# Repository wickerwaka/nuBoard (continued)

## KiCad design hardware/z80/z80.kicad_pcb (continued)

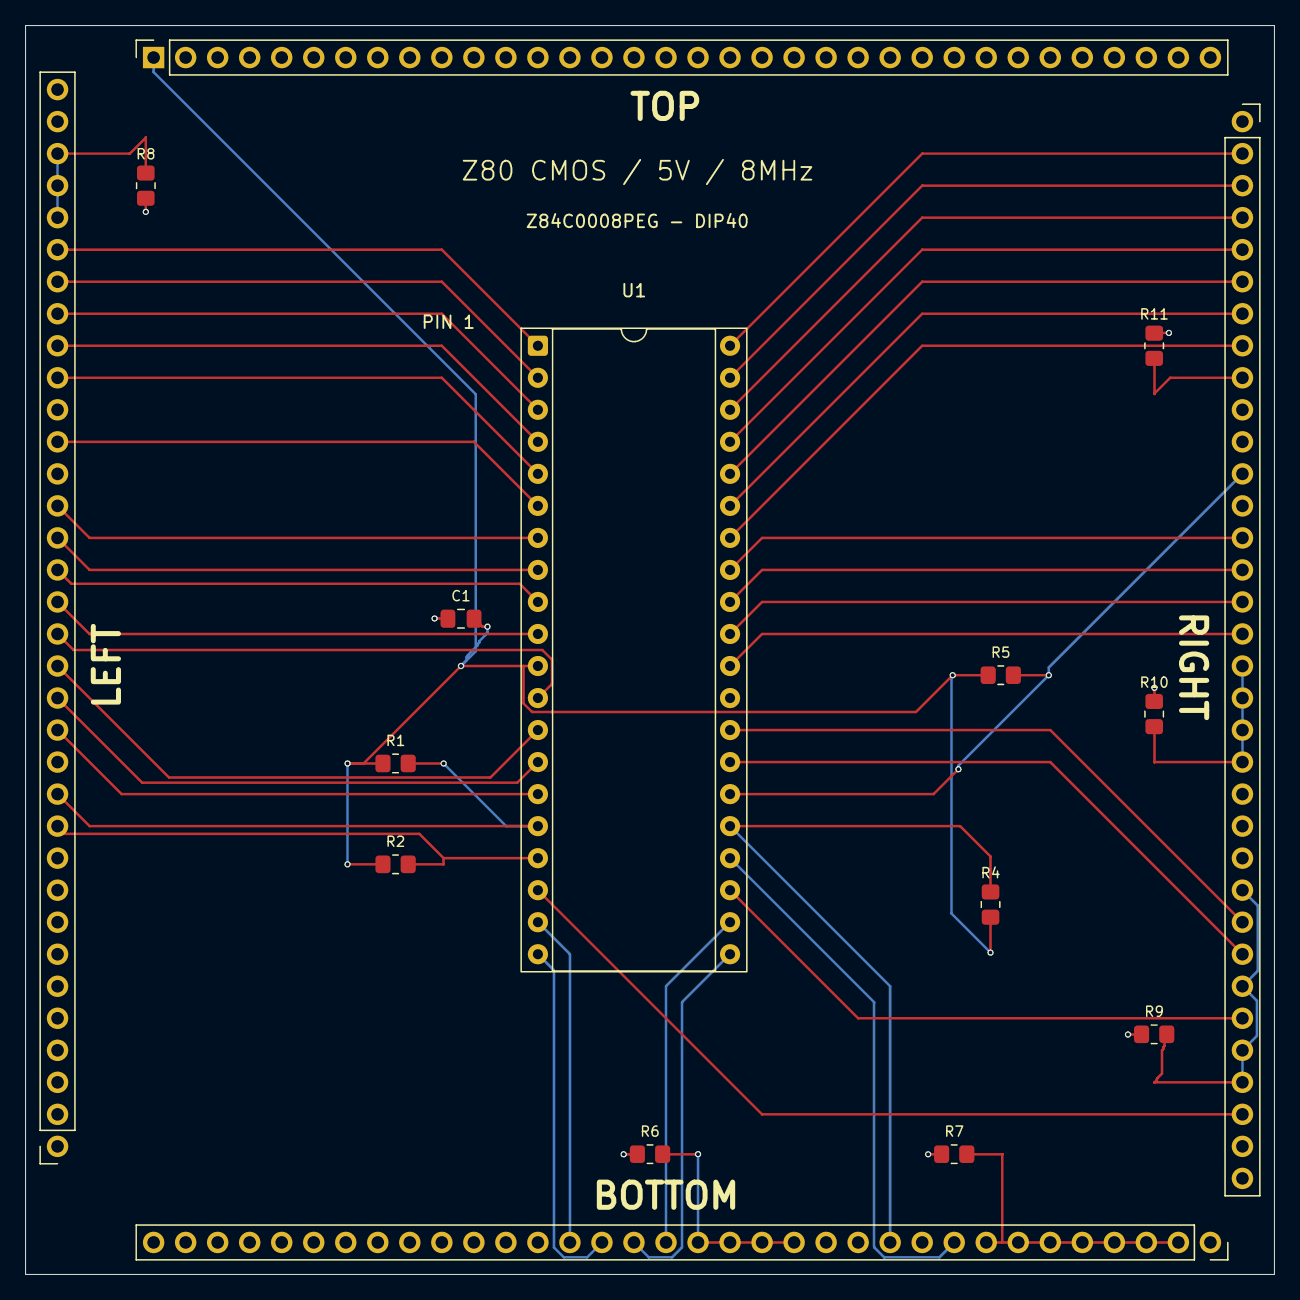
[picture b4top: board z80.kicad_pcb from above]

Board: 2 copper layers, 99.1 x 99.1 mm, 13 parts (0 on the bottom side), 46 nets.

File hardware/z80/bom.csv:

Reference,Quantity,Value/part,Package,Notes
U1,1,Z84C0008PEG,"DIP-40, 15.24mm rows",Use matching through-hole socket
C1,1,100nF ceramic 50V,0805 SMD HandSolder,Local supply bypass
R1 R2 R4 R5,4,10k >=0.25W,0805 SMD HandSolder,X0–X3 input pull-ups
J1,1,nuBoard mezzanine mating contact set,Four 34-position rows 2.54mm pitch,Match existing host
R6,1,47k 1% >=0.25W,0805 SMD HandSolder,B1 shared unused-bit pull-down to GND
R7,1,47k 1% >=0.25W,0805 SMD HandSolder,B2 shared unused-bit pull-down to GND
R8,1,47k 1% >=0.25W,0805 SMD HandSolder,L0 shared unused-bit pull-down to GND
R9,1,47k 1% >=0.25W,0805 SMD HandSolder,R0 shared unused-bit pull-down to GND
R10,1,47k 1% >=0.25W,0805 SMD HandSolder,R1 shared unused-bit pull-down to GND
R11,1,47k 1% >=0.25W,0805 SMD HandSolder,R2 shared unused-bit pull-down to GND

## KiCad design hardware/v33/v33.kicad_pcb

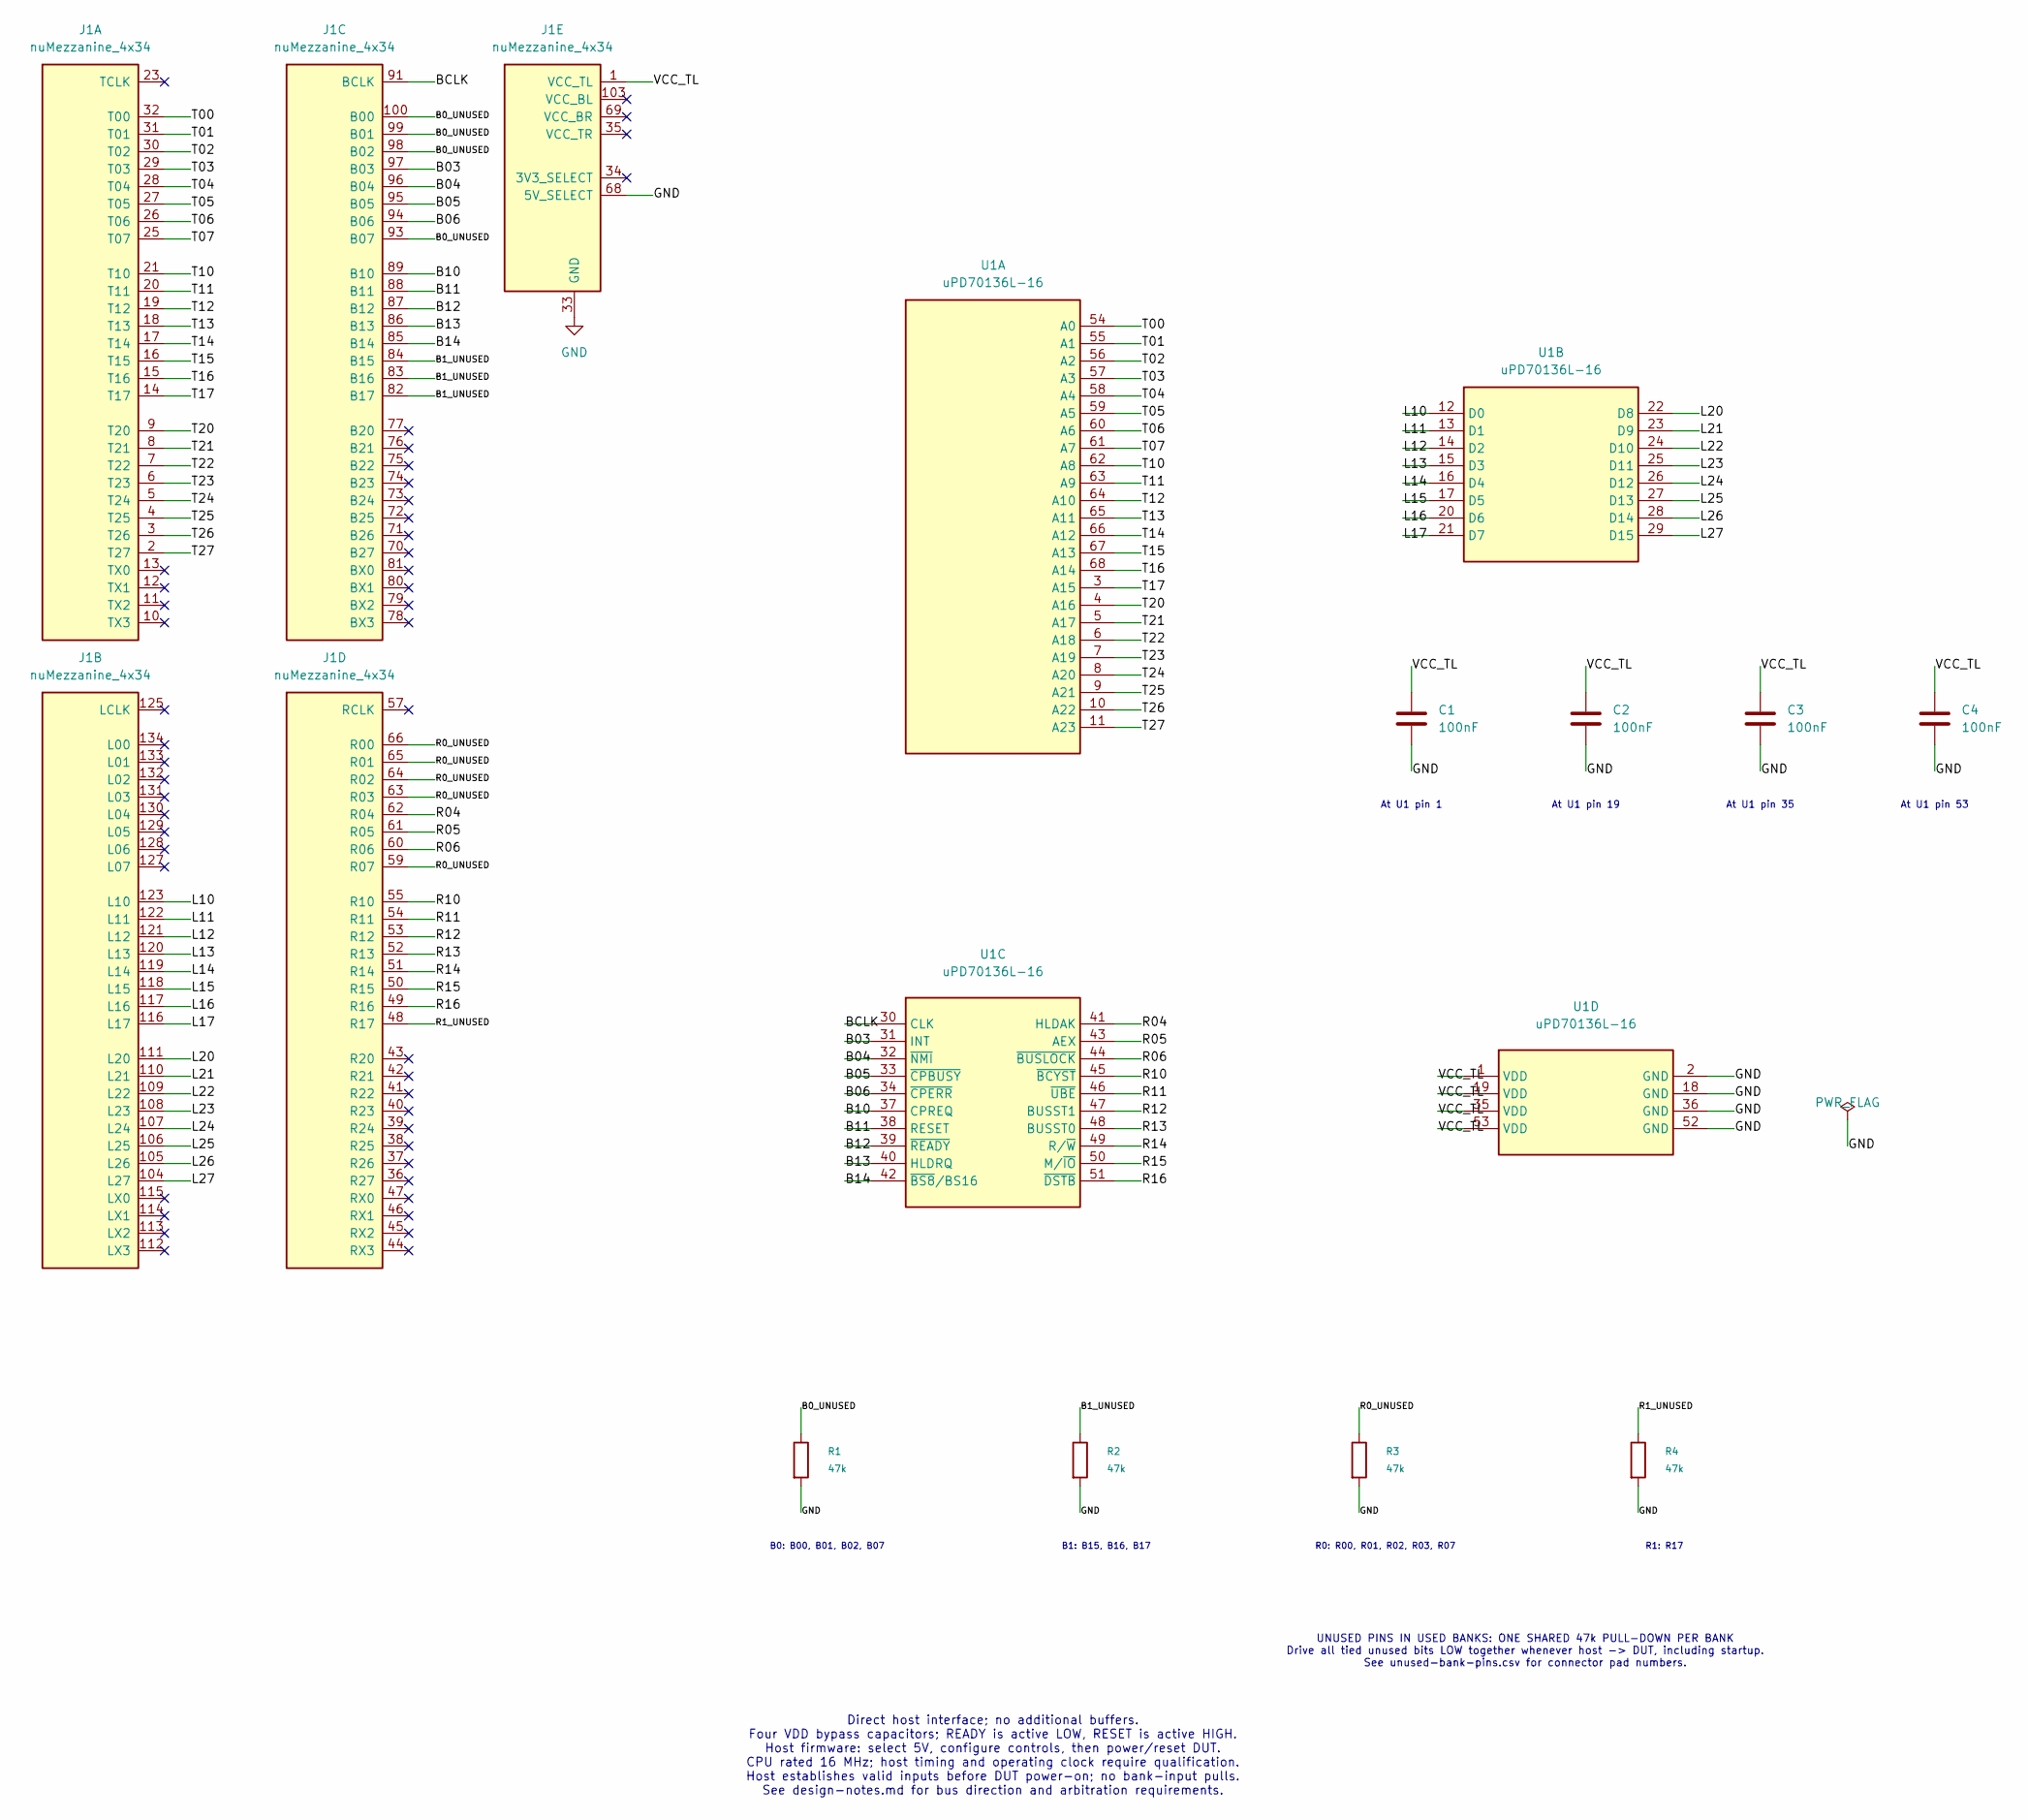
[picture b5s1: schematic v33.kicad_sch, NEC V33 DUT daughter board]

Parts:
C1, C2, C3, C4: 100nF; C_0805_2012Metric_Pad1.18x1.45mm_HandSolder; Voltage 50V
J1: nuMezzanine_4x34; nuMezzanine_4x34_P2.54mm
R1, R2, R3, R4: 47k; R_0805_2012Metric_Pad1.20x1.40mm_HandSolder
U1: uPD70136L-16; PLCC-68_THT-Socket

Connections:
/B0_UNUSED: J1.93 (B07_93), J1.98 (B02_98), J1.99 (B01_99), J1.100 (B00_100), R1.1
/B1_UNUSED: J1.82 (B17_82), J1.83 (B16_83), J1.84 (B15_84), R2.1
/B03: J1.97 (B03_97), U1.31 (INT)
/B04: J1.96 (B04_96), U1.32 (~NMI)
/B05: J1.95 (B05_95), U1.33 (~CPBUSY)
/B06: J1.94 (B06_94), U1.34 (~CPERR)
/B10: J1.89 (B10_89), U1.37 (CPREQ)
/B11: J1.88 (B11_88), U1.38 (RESET)
/B12: J1.87 (B12_87), U1.39 (~READY)
/B13: J1.86 (B13_86), U1.40 (HLDRQ)
/B14: J1.85 (B14_85), U1.42 (~BS8/BS16)
/BCLK: J1.91 (BCLK_91), U1.30 (CLK)
/L10: J1.123 (L10_123), U1.12 (D0)
/L11: J1.122 (L11_122), U1.13 (D1)
/L12: J1.121 (L12_121), U1.14 (D2)
/L13: J1.120 (L13_120), U1.15 (D3)
/L14: J1.119 (L14_119), U1.16 (D4)
/L15: J1.118 (L15_118), U1.17 (D5)
/L16: J1.117 (L16_117), U1.20 (D6)
/L17: J1.116 (L17_116), U1.21 (D7)
/L20: J1.111 (L20_111), U1.22 (D8)
/L21: J1.110 (L21_110), U1.23 (D9)
/L22: J1.109 (L22_109), U1.24 (D10)
/L23: J1.108 (L23_108), U1.25 (D11)
/L24: J1.107 (L24_107), U1.26 (D12)
/L25: J1.106 (L25_106), U1.27 (D13)
/L26: J1.105 (L26_105), U1.28 (D14)
/L27: J1.104 (L27_104), U1.29 (D15)
/R0_UNUSED: J1.59 (R07_59), J1.63 (R03_63), J1.64 (R02_64), J1.65 (R01_65), J1.66 (R00_66), R3.1
/R1_UNUSED: J1.48 (R17_48), R4.1
/R04: J1.62 (R04_62), U1.41 (HLDAK)
/R05: J1.61 (R05_61), U1.43 (AEX)
/R06: J1.60 (R06_60), U1.44 (~BUSLOCK)
/R10: J1.55 (R10_55), U1.45 (~BCYST)
/R11: J1.54 (R11_54), U1.46 (~UBE)
/R12: J1.53 (R12_53), U1.47 (BUSST1)
/R13: J1.52 (R13_52), U1.48 (BUSST0)
/R14: J1.51 (R14_51), U1.49 (R/~W)
/R15: J1.50 (R15_50), U1.50 (M/~IO)
/R16: J1.49 (R16_49), U1.51 (~DSTB)
/T00: J1.32 (T00_32), U1.54 (A0)
/T01: J1.31 (T01_31), U1.55 (A1)
/T02: J1.30 (T02_30), U1.56 (A2)
/T03: J1.29 (T03_29), U1.57 (A3)
/T04: J1.28 (T04_28), U1.58 (A4)
/T05: J1.27 (T05_27), U1.59 (A5)
/T06: J1.26 (T06_26), U1.60 (A6)
/T07: J1.25 (T07_25), U1.61 (A7)
/T10: J1.21 (T10_21), U1.62 (A8)
/T11: J1.20 (T11_20), U1.63 (A9)
/T12: J1.19 (T12_19), U1.64 (A10)
/T13: J1.18 (T13_18), U1.65 (A11)
/T14: J1.17 (T14_17), U1.66 (A12)
/T15: J1.16 (T15_16), U1.67 (A13)
/T16: J1.15 (T16_15), U1.68 (A14)
/T17: J1.14 (T17_14), U1.3 (A15)
/T20: J1.9 (T20_9), U1.4 (A16)
/T21: J1.8 (T21_8), U1.5 (A17)
/T22: J1.7 (T22_7), U1.6 (A18)
/T23: J1.6 (T23_6), U1.7 (A19)
/T24: J1.5 (T24_5), U1.8 (A20)
/T25: J1.4 (T25_4), U1.9 (A21)
/T26: J1.3 (T26_3), U1.10 (A22)
/T27: J1.2 (T27_2), U1.11 (A23)
/VCC_TL: C1.1, C2.1, C3.1, C4.1, J1.1 (VCC_TL_1), U1.1 (VDD), U1.19 (VDD), U1.35 (VDD), U1.53 (VDD)
GND: C1.2, C2.2, C3.2, C4.2, J1.22 (GND_22), J1.24 (GND_24), J1.33 (GND_33), J1.56 (GND_56), J1.58 (GND_58), J1.67 (GND_67), J1.68 (5V_SELECT_68), J1.90 (GND_90), J1.92 (GND_92), J1.101 (GND_101), J1.102 (GND), J1.124 (GND_124), J1.126 (GND_126), J1.135 (GND_135), J1.136 (GND), R1.2, R2.2, R3.2, R4.2, U1.2 (GND), U1.18 (GND), U1.36 (GND), U1.52 (GND)

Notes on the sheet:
At U1 pin 1
At U1 pin 19
At U1 pin 35
At U1 pin 53
Direct host interface; no additional buffers. Four VDD bypass capacitors; READY is active LOW, RESET is active HIGH. Host firmware: select 5V, configure controls, then power/reset DUT. CPU rated 16 MHz; host timing and operating clock require qualification. Host establishes valid inputs before DUT 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
B0: B00, B01, B02, B07
B1: B15, B16, B17
R0: R00, R01, R02, R03, R07
R1: R17
UNUSED PINS IN USED BANKS: ONE SHARED 47k PULL-DOWN PER BANK Drive all tied unused bits LOW together whenever host -> DUT, including startup. See unused-bank-pins.csv for connector pad numbers.

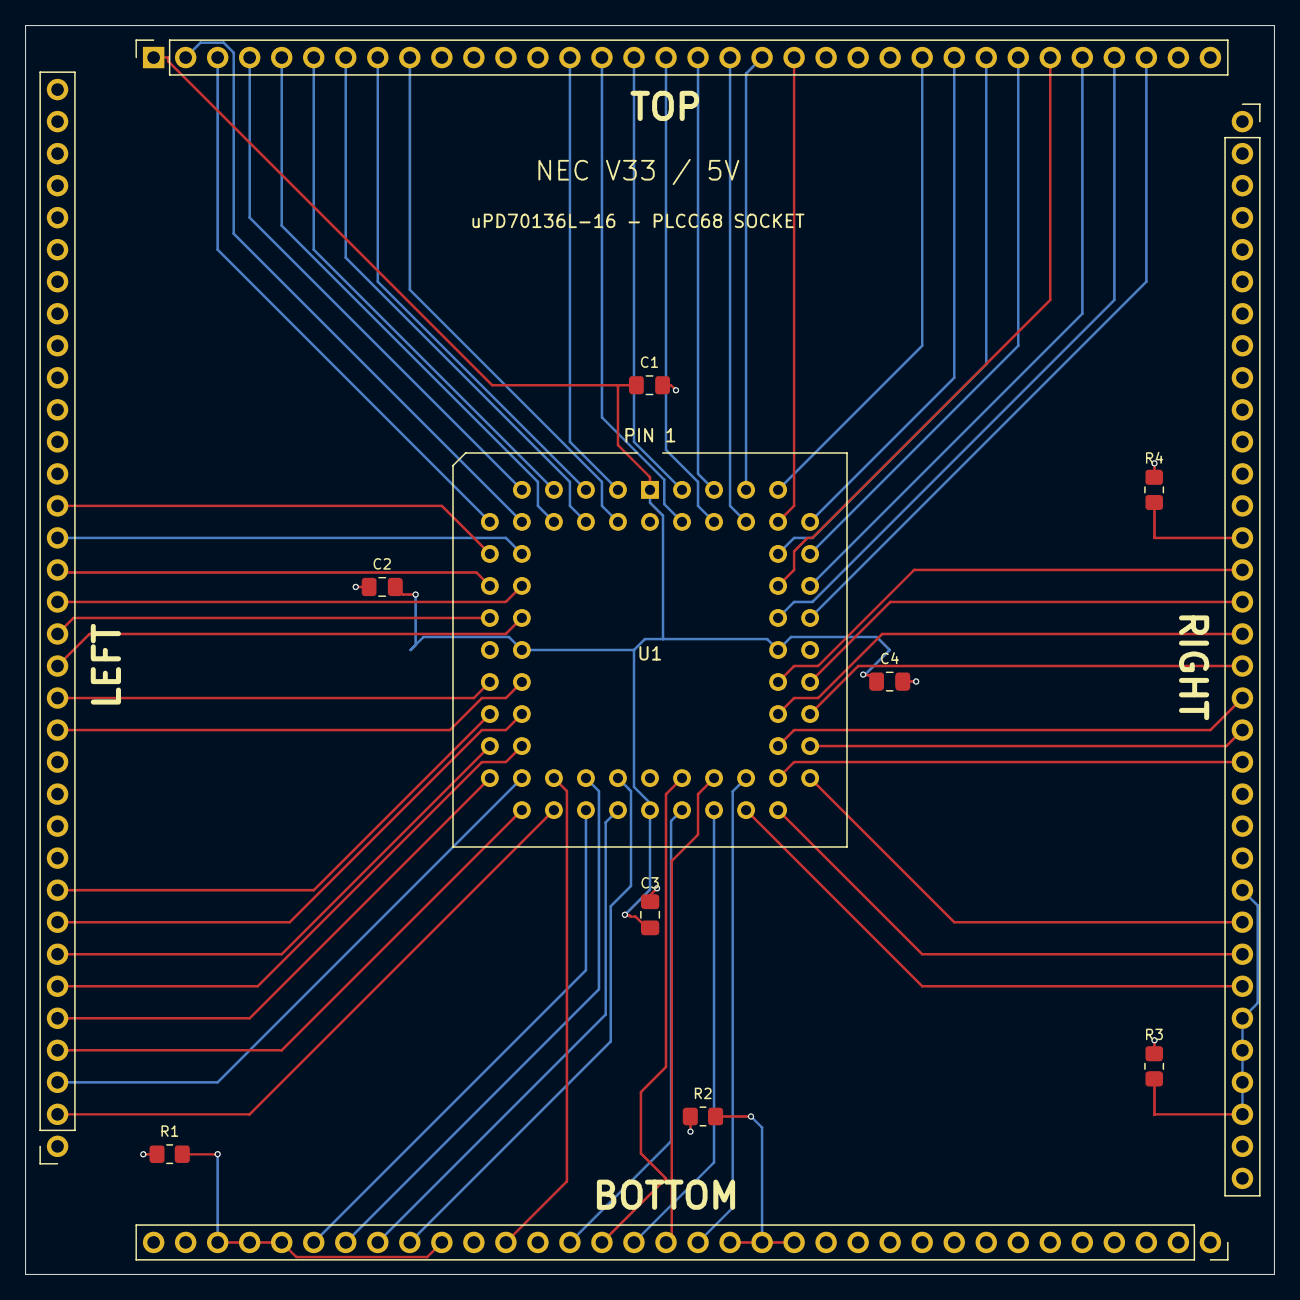
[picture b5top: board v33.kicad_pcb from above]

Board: 2 copper layers, 99.1 x 99.1 mm, 10 parts (0 on the bottom side), 66 nets.

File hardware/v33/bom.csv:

References,Quantity,Part / specification,Assembly note
U1,1,NEC uPD70136L-16,68-pin PLCC; user-supplied DUT
U1 socket,1,Assmann A-CCS 068-Z-T,Through-hole PLCC-68 socket; pin 1 toward TOP
C1 C2 C3 C4,4,"100 nF ceramic 50 V, 0805 SMD HandSolder",Enlarged hand-solder pads; top-side placement
J1,1,Template nuMezzanine_4x34 edge interface,Populate mating hardware to match existing host/template
R1,1,"47k 1% >=0.25W, 0805 SMD HandSolder",B0 shared unused-bit pull-down to GND
R2,1,"47k 1% >=0.25W, 0805 SMD HandSolder",B1 shared unused-bit pull-down to GND
R3,1,"47k 1% >=0.25W, 0805 SMD HandSolder",R0 shared unused-bit pull-down to GND
R4,1,"47k 1% >=0.25W, 0805 SMD HandSolder",R1 shared unused-bit pull-down to GND

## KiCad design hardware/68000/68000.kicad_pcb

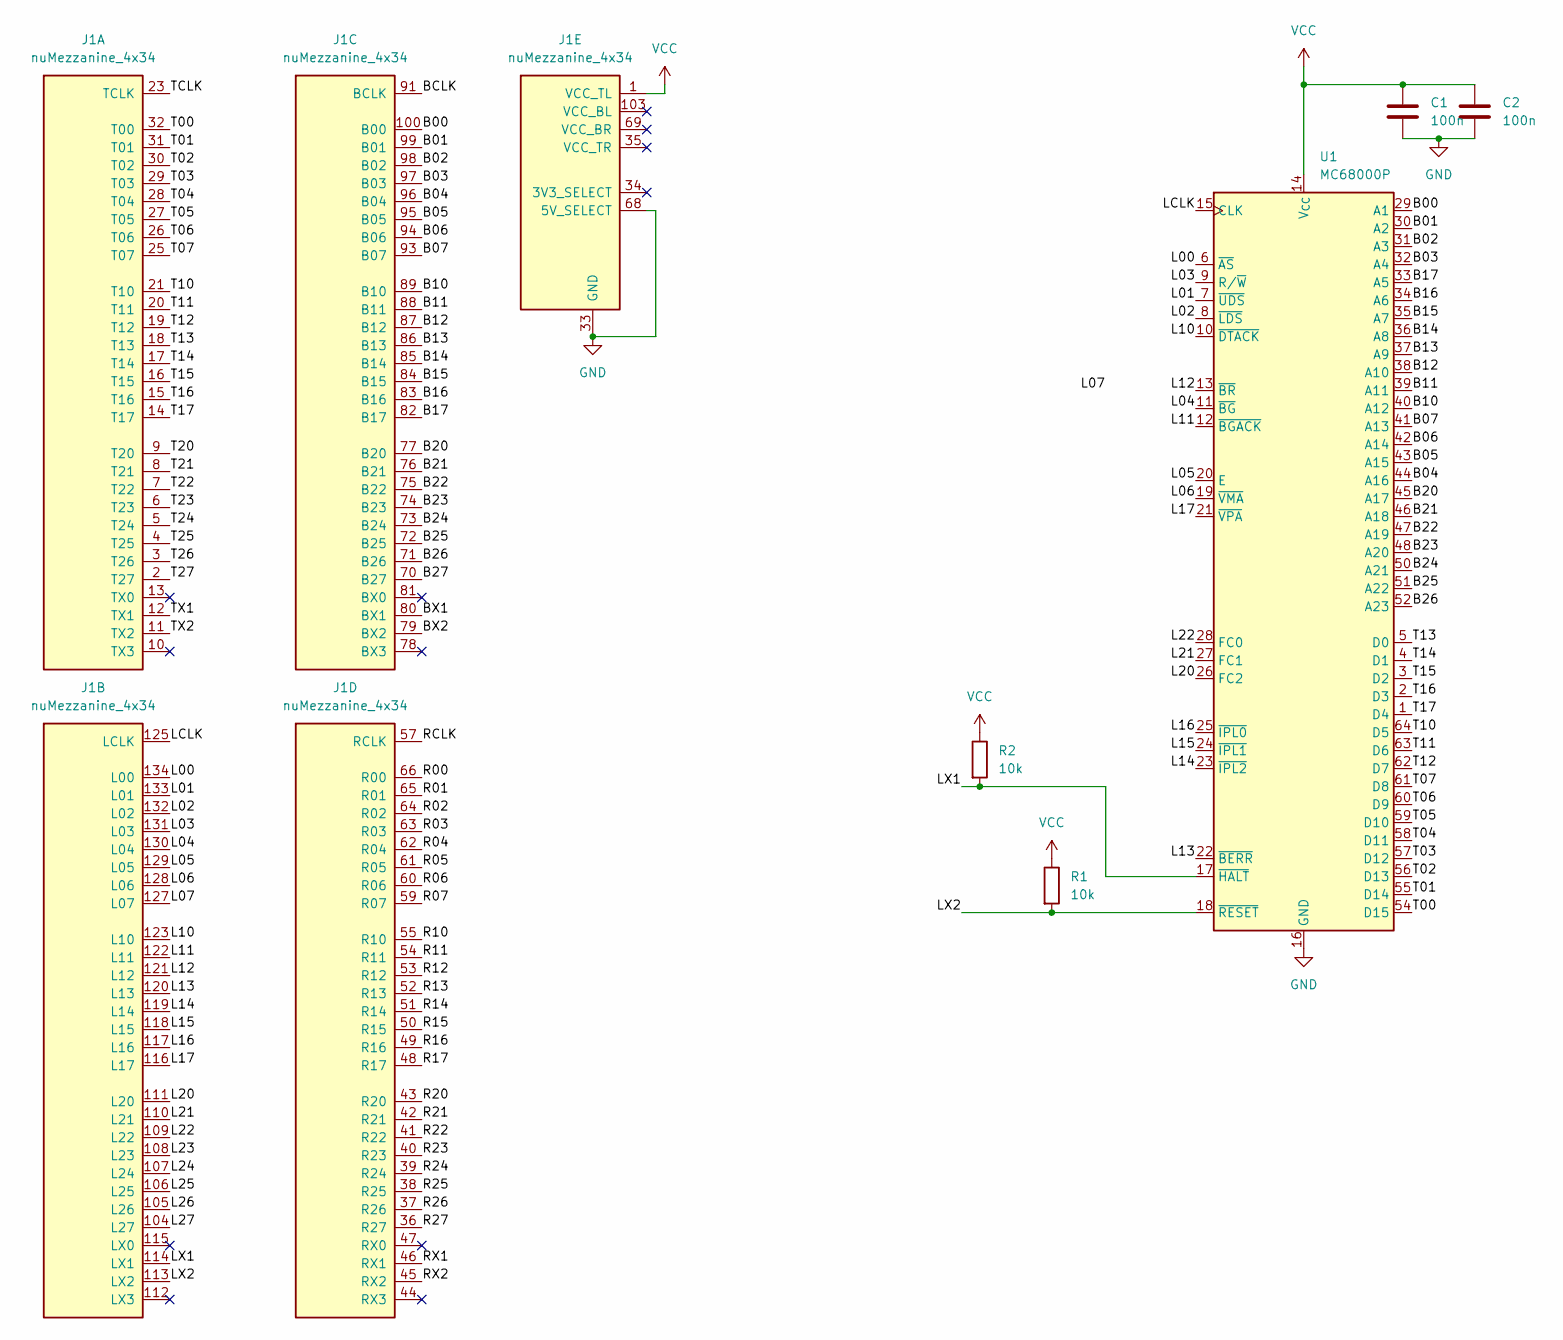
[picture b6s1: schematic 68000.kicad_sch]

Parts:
C1, C2: 100n; C_0805_2012Metric_Pad1.18x1.45mm_HandSolder
J1: nuMezzanine_4x34; nuMezzanine_4x34_P2.54mm
R1, R2: 10k; R_0805_2012Metric_Pad1.20x1.40mm_HandSolder
U1: MC68000P; DIP-64_W22.86mm

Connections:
/B00: J1.100 (B00_100), U1.29 (A1)
/B01: J1.99 (B01_99), U1.30 (A2)
/B02: J1.98 (B02_98), U1.31 (A3)
/B03: J1.97 (B03_97), U1.32 (A4)
/B04: J1.96 (B04_96), U1.44 (A16)
/B05: J1.95 (B05_95), U1.43 (A15)
/B06: J1.94 (B06_94), U1.42 (A14)
/B07: J1.93 (B07_93), U1.41 (A13)
/B10: J1.89 (B10_89), U1.40 (A12)
/B11: J1.88 (B11_88), U1.39 (A11)
/B12: J1.87 (B12_87), U1.38 (A10)
/B13: J1.86 (B13_86), U1.37 (A9)
/B14: J1.85 (B14_85), U1.36 (A8)
/B15: J1.84 (B15_84), U1.35 (A7)
/B16: J1.83 (B16_83), U1.34 (A6)
/B17: J1.82 (B17_82), U1.33 (A5)
/B20: J1.77 (B20_77), U1.45 (A17)
/B21: J1.76 (B21_76), U1.46 (A18)
/B22: J1.75 (B22_75), U1.47 (A19)
/B23: J1.74 (B23_74), U1.48 (A20)
/B24: J1.73 (B24_73), U1.50 (A21)
/B25: J1.72 (B25_72), U1.51 (A22)
/B26: J1.71 (B26_71), U1.52 (A23)
/B27: J1.70 (B27_70)
/BCLK: J1.91 (BCLK_91)
/BX1: J1.80 (BX1_80)
/BX2: J1.79 (BX2_79)
/L00: J1.134 (L00_134), U1.6 (~AS)
/L01: J1.133 (L01_133), U1.7 (~UDS)
/L02: J1.132 (L02_132), U1.8 (~LDS)
/L03: J1.131 (L03_131), U1.9 (R/~W)
/L04: J1.130 (L04_130), U1.11 (~BG)
/L05: J1.129 (L05_129), U1.20 (E)
/L06: J1.128 (L06_128), U1.19 (~VMA)
/L07: J1.127 (L07_127)
/L10: J1.123 (L10_123), U1.10 (~DTACK)
/L11: J1.122 (L11_122), U1.12 (~BGACK)
/L12: J1.121 (L12_121), U1.13 (~BR)
/L13: J1.120 (L13_120), U1.22 (~BERR)
/L14: J1.119 (L14_119), U1.23 (~IPL2)
/L15: J1.118 (L15_118), U1.24 (~IPL1)
/L16: J1.117 (L16_117), U1.25 (~IPL0)
/L17: J1.116 (L17_116), U1.21 (~VPA)
/L20: J1.111 (L20_111), U1.26 (FC2)
/L21: J1.110 (L21_110), U1.27 (FC1)
/L22: J1.109 (L22_109), U1.28 (FC0)
/L23: J1.108 (L23_108)
/L24: J1.107 (L24_107)
/L25: J1.106 (L25_106)
/L26: J1.105 (L26_105)
/L27: J1.104 (L27_104)
/LCLK: J1.125 (LCLK_125), U1.15 (CLK)
/LX1: J1.114 (LX1_114), R2.2, U1.17 (~HALT)
/LX2: J1.113 (LX2_113), R1.2, U1.18 (~RESET)
/R00: J1.66 (R00_66)
/R01: J1.65 (R01_65)
/R02: J1.64 (R02_64)
/R03: J1.63 (R03_63)
/R04: J1.62 (R04_62)
/R05: J1.61 (R05_61)
/R06: J1.60 (R06_60)
/R07: J1.59 (R07_59)
/R10: J1.55 (R10_55)
/R11: J1.54 (R11_54)
/R12: J1.53 (R12_53)
/R13: J1.52 (R13_52)
/R14: J1.51 (R14_51)
/R15: J1.50 (R15_50)
/R16: J1.49 (R16_49)
/R17: J1.48 (R17_48)
/R20: J1.43 (R20_43)
/R21: J1.42 (R21_42)
/R22: J1.41 (R22_41)
/R23: J1.40 (R23_40)
/R24: J1.39 (R24_39)
/R25: J1.38 (R25_38)
/R26: J1.37 (R26_37)
/R27: J1.36 (R27_36)
/RCLK: J1.57 (RCLK_57)
/RX1: J1.46 (RX1_46)
/RX2: J1.45 (RX2_45)
/T00: J1.32 (T00_32), U1.54 (D15)
/T01: J1.31 (T01_31), U1.55 (D14)
/T02: J1.30 (T02_30), U1.56 (D13)
/T03: J1.29 (T03_29), U1.57 (D12)
/T04: J1.28 (T04_28), U1.58 (D11)
/T05: J1.27 (T05_27), U1.59 (D10)
/T06: J1.26 (T06_26), U1.60 (D9)
/T07: J1.25 (T07_25), U1.61 (D8)
/T10: J1.21 (T10_21), U1.64 (D5)
/T11: J1.20 (T11_20), U1.63 (D6)
/T12: J1.19 (T12_19), U1.62 (D7)
/T13: J1.18 (T13_18), U1.5 (D0)
/T14: J1.17 (T14_17), U1.4 (D1)
/T15: J1.16 (T15_16), U1.3 (D2)
/T16: J1.15 (T16_15), U1.2 (D3)
/T17: J1.14 (T17_14), U1.1 (D4)
/T20: J1.9 (T20_9)
/T21: J1.8 (T21_8)
/T22: J1.7 (T22_7)
/T23: J1.6 (T23_6)
/T24: J1.5 (T24_5)
/T25: J1.4 (T25_4)
/T26: J1.3 (T26_3)
/T27: J1.2 (T27_2)
/TCLK: J1.23 (TCLK_23)
/TX1: J1.12 (TX1_12)
/TX2: J1.11 (TX2_11)
GND: C1.2, C2.2, J1.22 (GND_22), J1.24 (GND_24), J1.33 (GND_33), J1.56 (GND_56), J1.58 (GND_58), J1.67 (GND_67), J1.68 (5V_SELECT_68), J1.90 (GND_90), J1.92 (GND_92), J1.101 (GND_101), J1.102 (GND), J1.124 (GND_124), J1.126 (GND_126), J1.135 (GND_135), J1.136 (GND), U1.16 (GND), U1.53 (GND)
VCC: C1.1, C2.1, J1.1 (VCC_TL_1), R1.1, R2.1, U1.14 (V_{CC}), U1.49 (V_{CC})

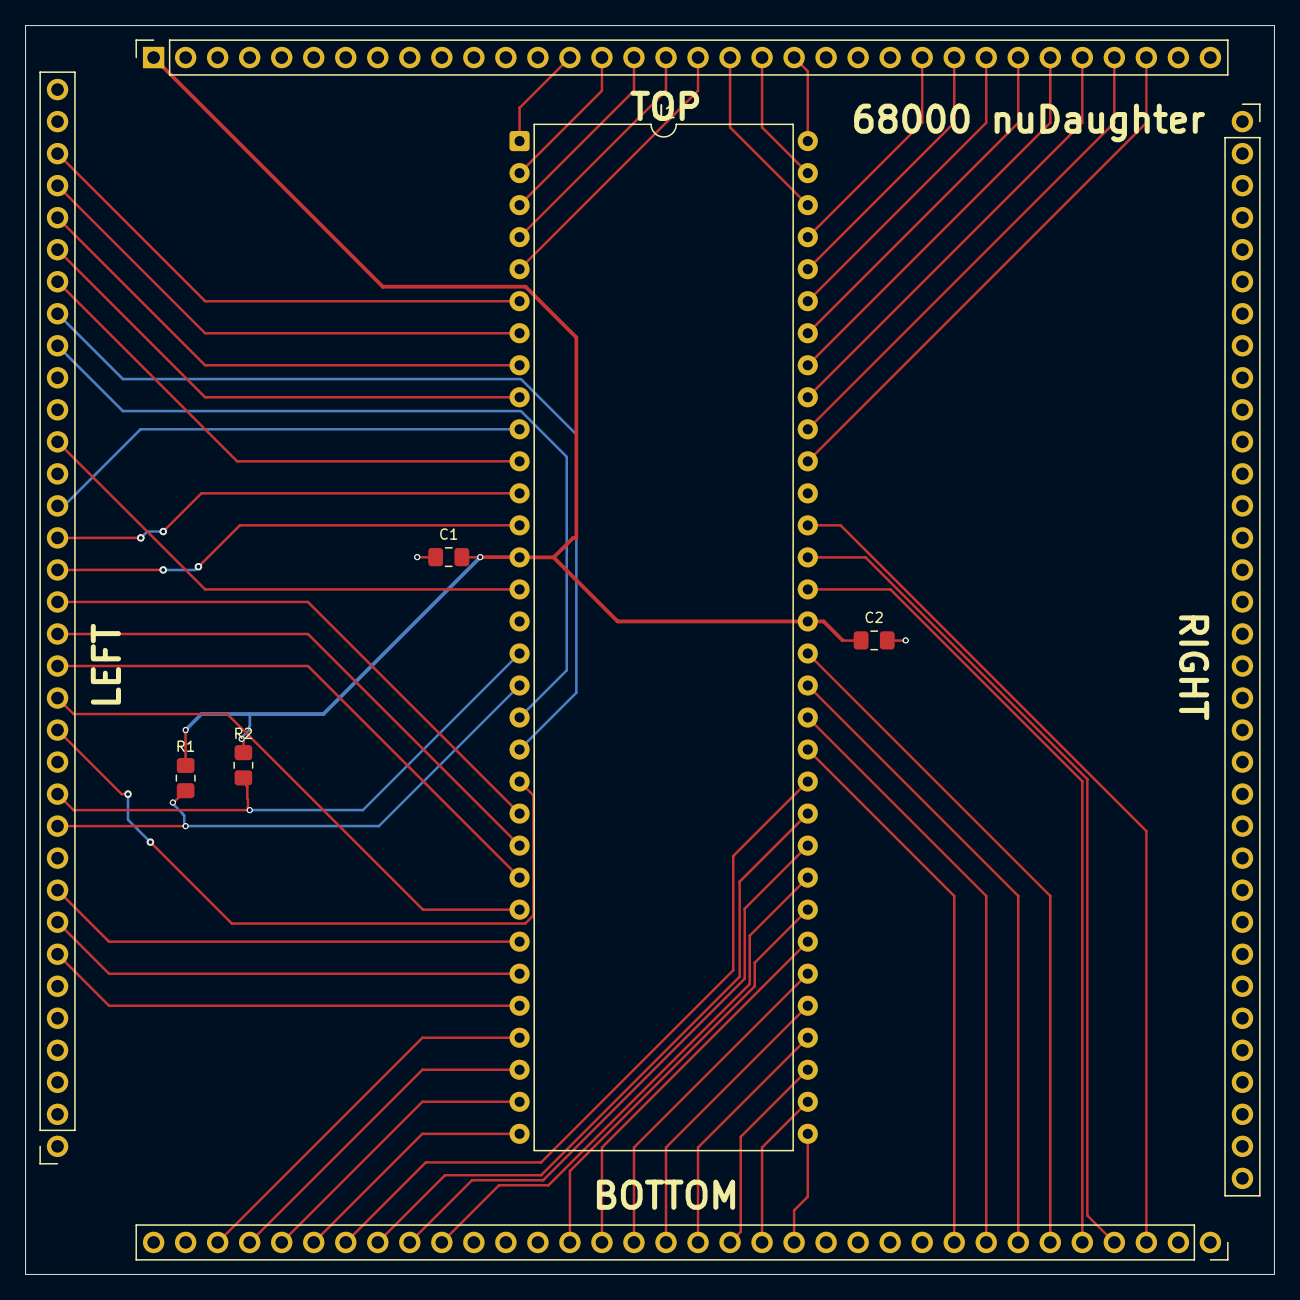
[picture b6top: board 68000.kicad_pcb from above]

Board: 2 copper layers, 99.1 x 99.1 mm, 6 parts (0 on the bottom side), 62 nets.

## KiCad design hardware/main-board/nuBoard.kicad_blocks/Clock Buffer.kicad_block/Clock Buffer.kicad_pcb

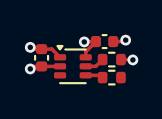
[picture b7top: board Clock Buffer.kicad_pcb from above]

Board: 6 copper layers, 5 parts (0 on the bottom side), 5 nets.

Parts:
C211, C212: 0.1u; C_0402_1005Metric
R57: 10K; R_0402_1005Metric
R58: 22; R_0402_1005Metric
U20: SN74LVC1T45DRL; SOT-563

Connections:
+3.3V: C211.1, U20.1 (VCCA)
/F_TCLK_EN: R57.1, U20.5 (DIR)
GND: C211.2, C212.2, R57.2, U20.2 (GND)
unnamed: R58.1, U20.4 (B)
VCCB: C212.1, U20.6 (VCCB)

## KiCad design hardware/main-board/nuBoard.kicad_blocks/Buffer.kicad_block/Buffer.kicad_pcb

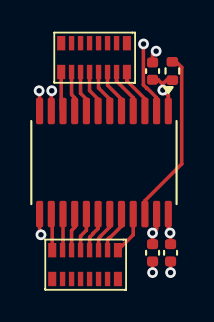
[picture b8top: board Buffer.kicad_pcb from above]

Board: 8 copper layers, 7 parts (0 on the bottom side), 20 nets.

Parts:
C68, C69, C70: 0.1u; C_0402_1005Metric
R35: 10K; R_0402_1005Metric
RN23, RN24: 22R; YC248-JR-0722RL
U24: SN74LVCH8T245PWR; TSSOP-24_4.4x7.8mm_P0.65mm

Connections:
+3.3V: C68.1, R35.1, U24.1 (VCCA)
/~F_B0_OE: R35.2, U24.22 (~OE)
GND: C68.2, C69.2, C70.2, U24.11 (GND), U24.12 (GND), U24.13 (GND)
unnamed: RN23.16, U24.3 (A1)
unnamed: RN23.15, U24.4 (A2)
unnamed: RN23.14, U24.5 (A3)
unnamed: RN23.13, U24.6 (A4)
unnamed: RN23.12, U24.7 (A5)
unnamed: RN23.11, U24.8 (A6)
unnamed: RN23.10, U24.9 (A7)
unnamed: RN23.9, U24.10 (A8)
unnamed: RN24.1, U24.21 (B1)
unnamed: RN24.2, U24.20 (B2)
unnamed: RN24.3, U24.19 (B3)
unnamed: RN24.4, U24.18 (B4)
unnamed: RN24.5, U24.17 (B5)
unnamed: RN24.6, U24.16 (B6)
unnamed: RN24.7, U24.15 (B7)
unnamed: RN24.8, U24.14 (B8)
VCCB: C69.1, C70.1, U24.23 (VCCB), U24.24 (VCCB)
